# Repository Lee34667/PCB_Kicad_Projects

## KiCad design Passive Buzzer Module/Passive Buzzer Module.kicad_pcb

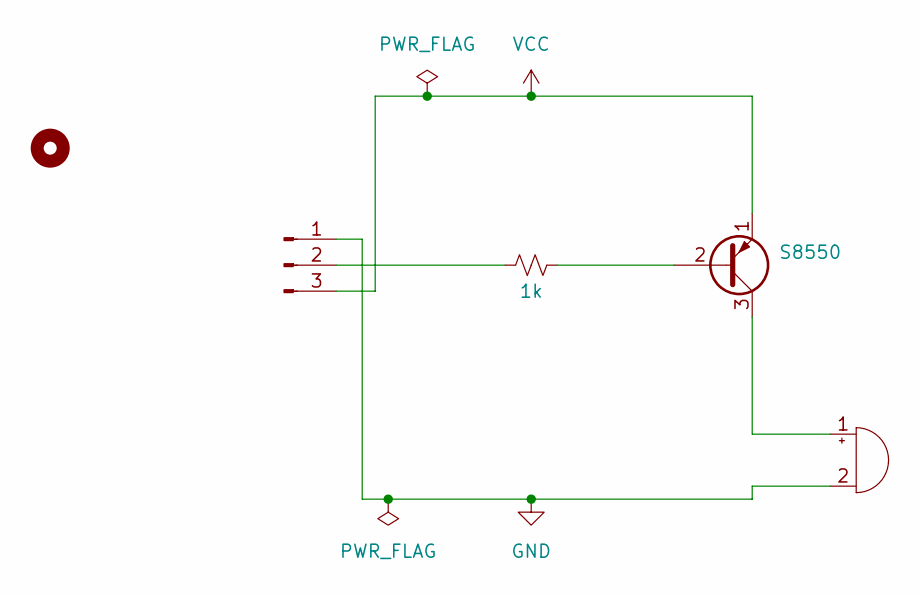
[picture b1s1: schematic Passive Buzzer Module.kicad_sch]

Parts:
BZ1: Buzzer; Buzzer_12x9.5RM7.6
H1: MountingHole; MountingHole_2.1mm
J1: Conn_01x03_Pin; PinHeader_1x03_P2.54mm_Horizontal
Q1: S8550; TO-92_HandSolder
R1: 1k; R_0201_0603Metric

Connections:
GND: BZ1.2 (-), J1.1
unnamed: BZ1.1 (+), Q1.3 (C)
unnamed: J1.2, R1.1
unnamed: Q1.2 (B), R1.2
VCC: J1.3, Q1.1 (E)

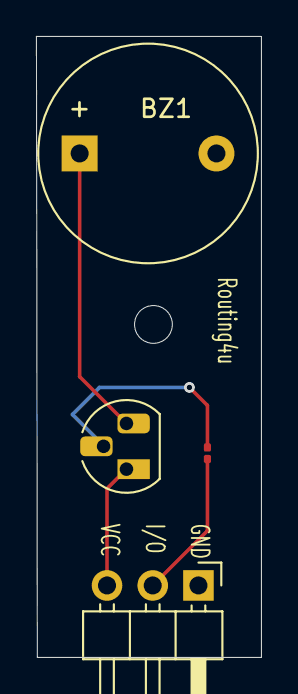
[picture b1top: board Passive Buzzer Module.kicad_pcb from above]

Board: 4 copper layers, 12.5 x 34.5 mm, 5 parts (0 on the bottom side), 5 nets.

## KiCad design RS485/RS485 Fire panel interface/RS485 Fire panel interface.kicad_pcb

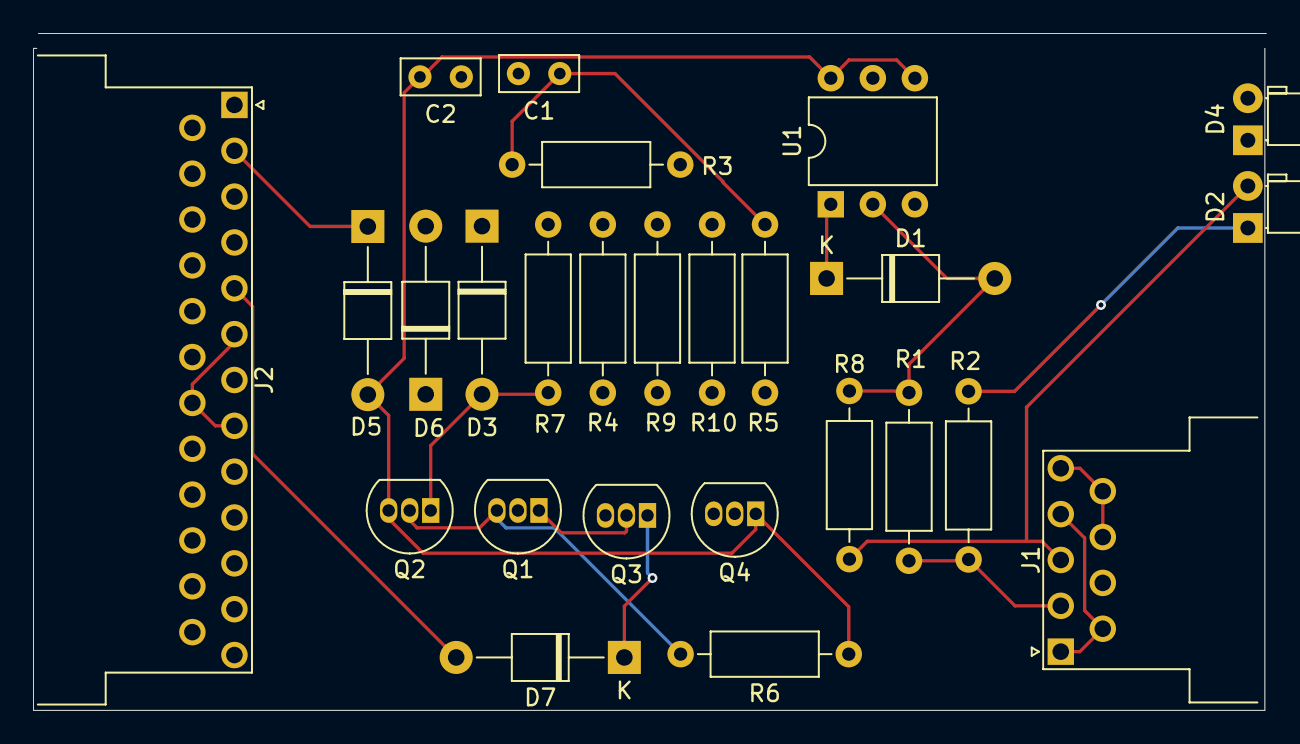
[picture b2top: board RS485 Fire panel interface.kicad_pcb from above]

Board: 2 copper layers, 74.5 x 40.9 mm, 26 parts (0 on the bottom side), 21 nets.

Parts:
C1, C2: 22uF 16V; C_Rect_L4.6mm_W2.0mm_P2.50mm_MKS02_FKP02
D1, D3, D5, D6, D7: D_Filled; D_T-1_P10.16mm_Horizontal
D2: Rx; LED_D3.0mm_Horizontal_O1.27mm_Z2.0mm
D4: Tx; LED_D3.0mm_Horizontal_O1.27mm_Z2.0mm
J1: DE9_Plug; DSUB-9_Male_Horizontal_P2.77x2.54mm_EdgePinOffset9.40mm
J2: DB25_Receptacle; DSUB-25_Male_Horizontal_P2.77x2.54mm_EdgePinOffset9.40mm
Q1, Q2, Q3: BC547; TO-92_Inline
Q4: BC557; TO-92_Inline
R1: 220R; R_Axial_DIN0207_L6.3mm_D2.5mm_P10.16mm_Horizontal
R2: 1k; R_Axial_DIN0207_L6.3mm_D2.5mm_P10.16mm_Horizontal
R3, R4, R5, R6, R7, R8, R9, R10: 2k2; R_Axial_DIN0207_L6.3mm_D2.5mm_P10.16mm_Horizontal
U1: 4N35; DIP-6_W7.62mm

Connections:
GND: C1.2, C2.1, J2.7
unnamed: D1.2 (A), R1.2, R8.1, U1.2
unnamed: D1.1 (K), D2.2 (A), J1.3, R8.2, U1.1
unnamed: D2.1 (K), R2.2
unnamed: D3.2 (A), Q2.1 (C), R7.1
unnamed: D3.1 (K), Q1.2 (B), R4.1, U1.5
unnamed: D4.2 (A), Q3.3 (E)
unnamed: D4.1 (K), R9.2
unnamed: C2.2, D5.2 (A), Q2.3 (E), Q4.1 (C), R6.1, U1.4, U1.6
unnamed: D5.1 (K), J2.2
unnamed: D6.2 (A), J2.6, J2.8, J2.20
unnamed: C1.1, D6.1 (K), D7.1 (K), Q3.1 (C), R3.2, R5.2
unnamed: D7.2 (A), J2.4, J2.5
unnamed: J1.1, J1.4, J1.6
unnamed: J1.2, R1.1, R2.1
unnamed: J1.5, J1.8, J1.9
unnamed: J2.3, R9.1, R10.2
unnamed: Q1.1 (C), Q3.2 (B), Q4.2 (B), R5.1
unnamed: Q1.3 (E), Q2.2 (B), R6.2
unnamed: Q4.3 (E), R10.1
unnamed: R3.1, R4.2, R7.2

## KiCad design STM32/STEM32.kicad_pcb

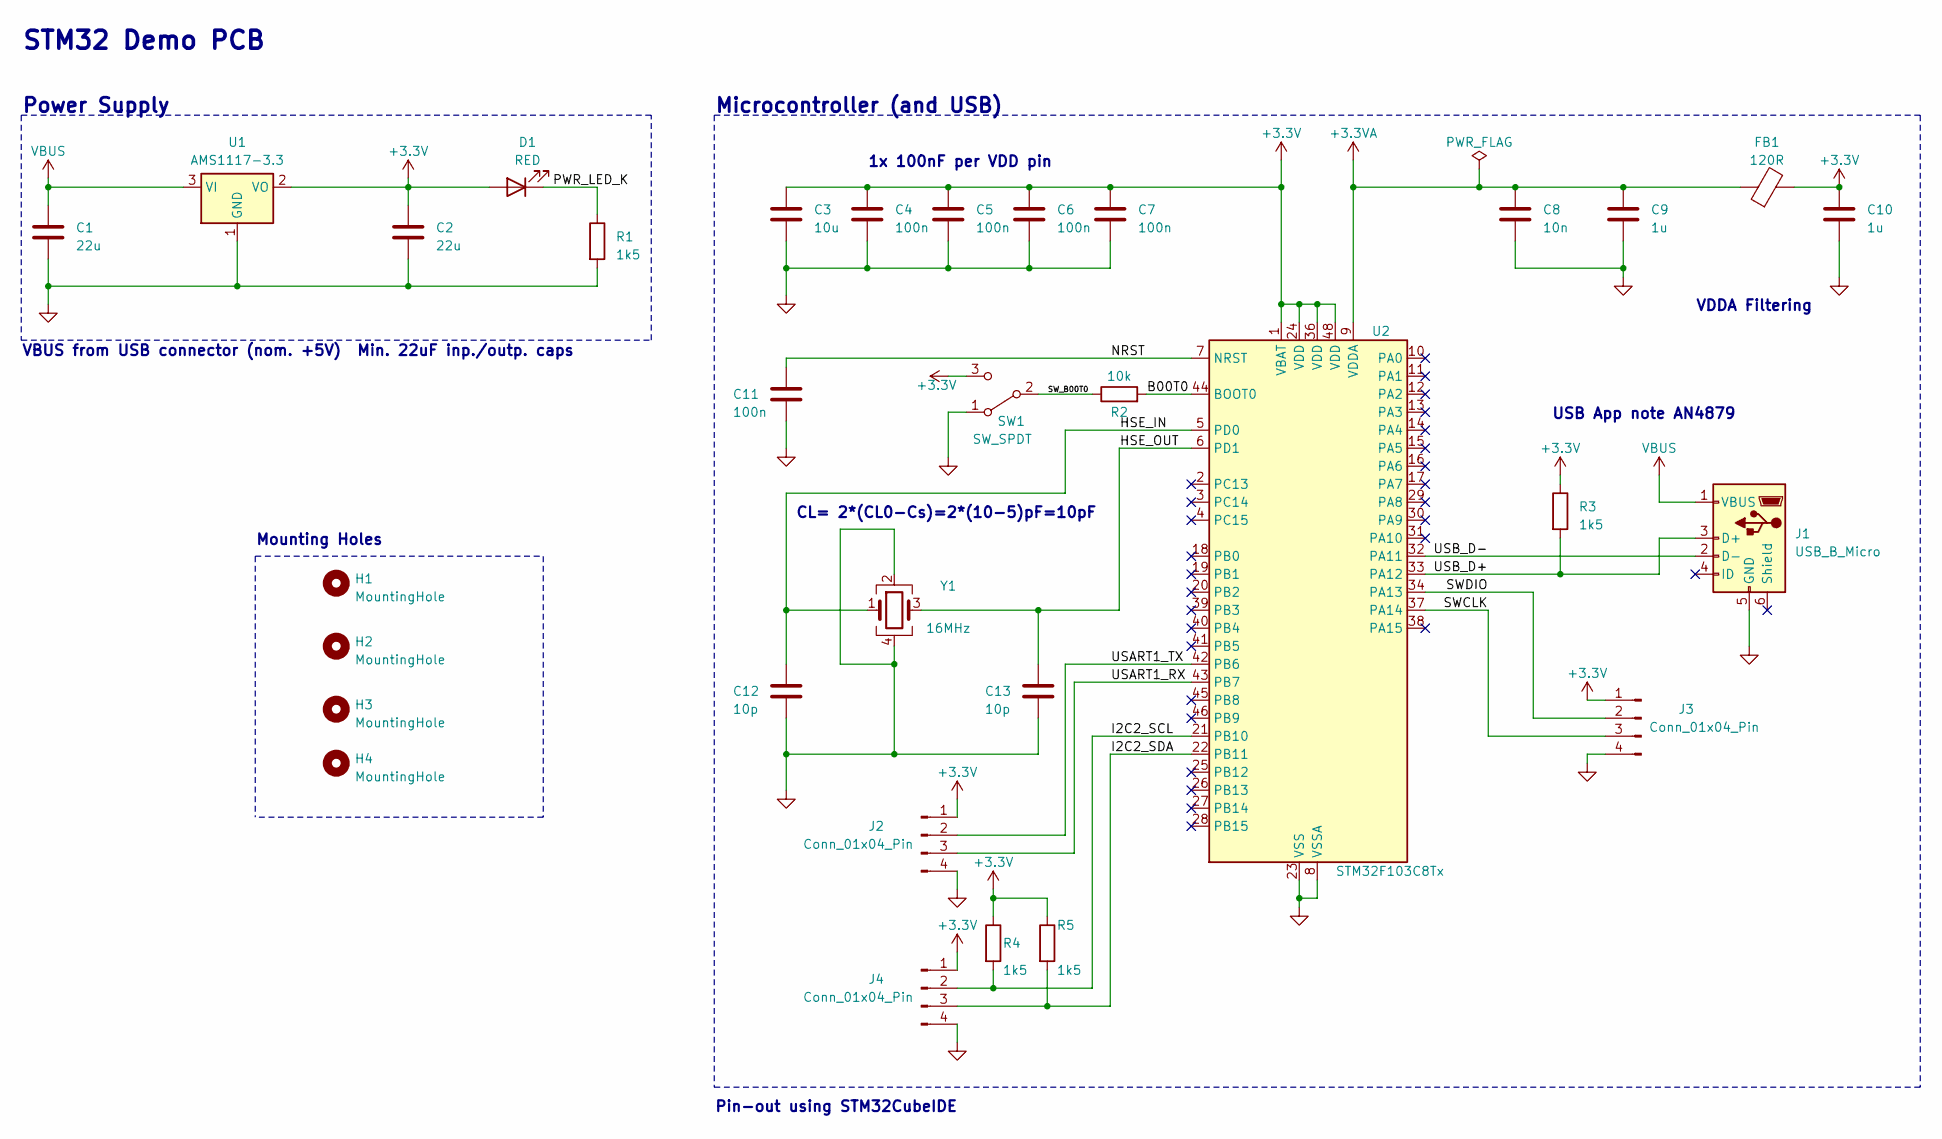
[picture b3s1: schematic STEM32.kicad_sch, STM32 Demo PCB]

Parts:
C1, C2: 22u; C_0805_2012Metric
C3: 10u; C_0603_1608Metric
C4, C5, C6, C7, C11: 100n; C_0402_1005Metric
C8: 10n; C_0402_1005Metric
C9, C10: 1u; C_0402_1005Metric
C12, C13: 10p; C_0402_1005Metric
D1: RED; LED_0603_1608Metric
FB1: 120R; L_0603_1608Metric
H1, H2, H3, H4: MountingHole; MountingHole_2.2mm_M2
J1: USB_B_Micro; USB_Micro-B_Wuerth_629105150521
J2, J3, J4: Conn_01x04_Pin; PinHeader_1x04_P2.54mm_Vertical
R1, R3, R4, R5: 1k5; R_0402_1005Metric
R2: 10k; R_0402_1005Metric
SW1: SW_SPDT; SW_SPDT_PCM12
U1: AMS1117-3.3; SOT-223-3_TabPin2
U2: STM32F103C8Tx; LQFP-48_7x7mm_P0.5mm
Y1: 16MHz; Crystal_SMD_3225-4Pin_3.2x2.5mm

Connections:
+3.3V: C2.1, C3.1, C4.1, C5.1, C6.1, C7.1, C10.1, D1.2 (A), FB1.2, J2.1, J3.1, J4.1, R3.1, R4.1, R5.1, SW1.3 (C), U1.2 (VO), U2.1 (VBAT), U2.24 (VDD), U2.36 (VDD), U2.48 (VDD)
+3.3VA: C8.1, C9.1, FB1.1, U2.9 (VDDA)
/B00T0: R2.2, U2.44 (BOOT0)
/HSE_IN: C12.1, U2.5 (PD0), Y1.1
/HSE_OUT: C13.1, U2.6 (PD1), Y1.3
/I2C2_SCL: J4.2, R4.2, U2.21 (PB10)
/I2C2_SDA: J4.3, R5.2, U2.22 (PB11)
/NRST: C11.1, U2.7 (NRST)
/PWR_LED_K: D1.1 (K), R1.1
/SWCLK: J3.3, U2.37 (PA14)
/SWDIO: J3.2, U2.34 (PA13)
/SW_B00T0: R2.1, SW1.2 (B)
/USART1_RX: J2.3, U2.43 (PB7)
/USART1_TX: J2.2, U2.42 (PB6)
/USB_D+: J1.3 (D+), R3.2, U2.33 (PA12)
/USB_D-: J1.2 (D-), U2.32 (PA11)
GND: C1.2, C2.2, C3.2, C4.2, C5.2, C6.2, C7.2, C8.2, C9.2, C10.2, C11.2, C12.2, C13.2, J1.5 (GND), J2.4, J3.4, J4.4, R1.2, SW1.1 (A), U1.1 (GND), U2.8 (VSSA), U2.23 (VSS), U2.35 (VSS), U2.47 (VSS), Y1.2, Y1.4
VBUS: C1.1, J1.1 (VBUS), U1.3 (VI)

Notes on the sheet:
VBUS from USB connector (nom. +5V) Min. 22uF inp./outp. caps
USB App note AN4879
1x 100nF per VDD pin
Microcontroller (and USB)
VDDA Filtering
Mounting Holes
CL= 2*(CL0-Cs)=2*(10-5)pF=10pF
Pin-out using STM32CubeIDE
Power Supply
STM32 Demo PCB

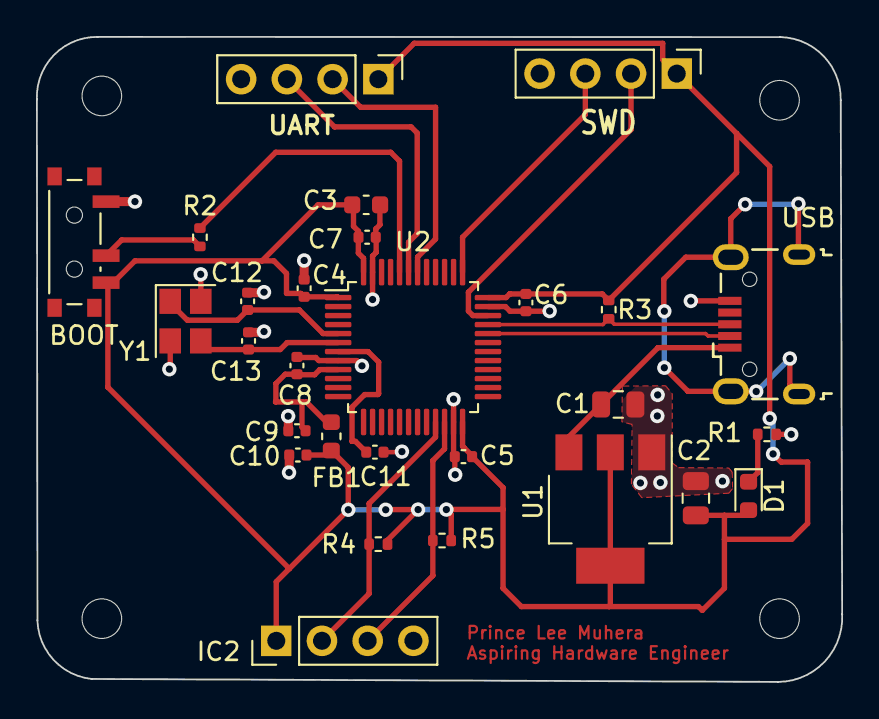
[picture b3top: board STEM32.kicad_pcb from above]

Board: 2 copper layers, 44.7 x 35.8 mm, 32 parts (0 on the bottom side), 18 nets.

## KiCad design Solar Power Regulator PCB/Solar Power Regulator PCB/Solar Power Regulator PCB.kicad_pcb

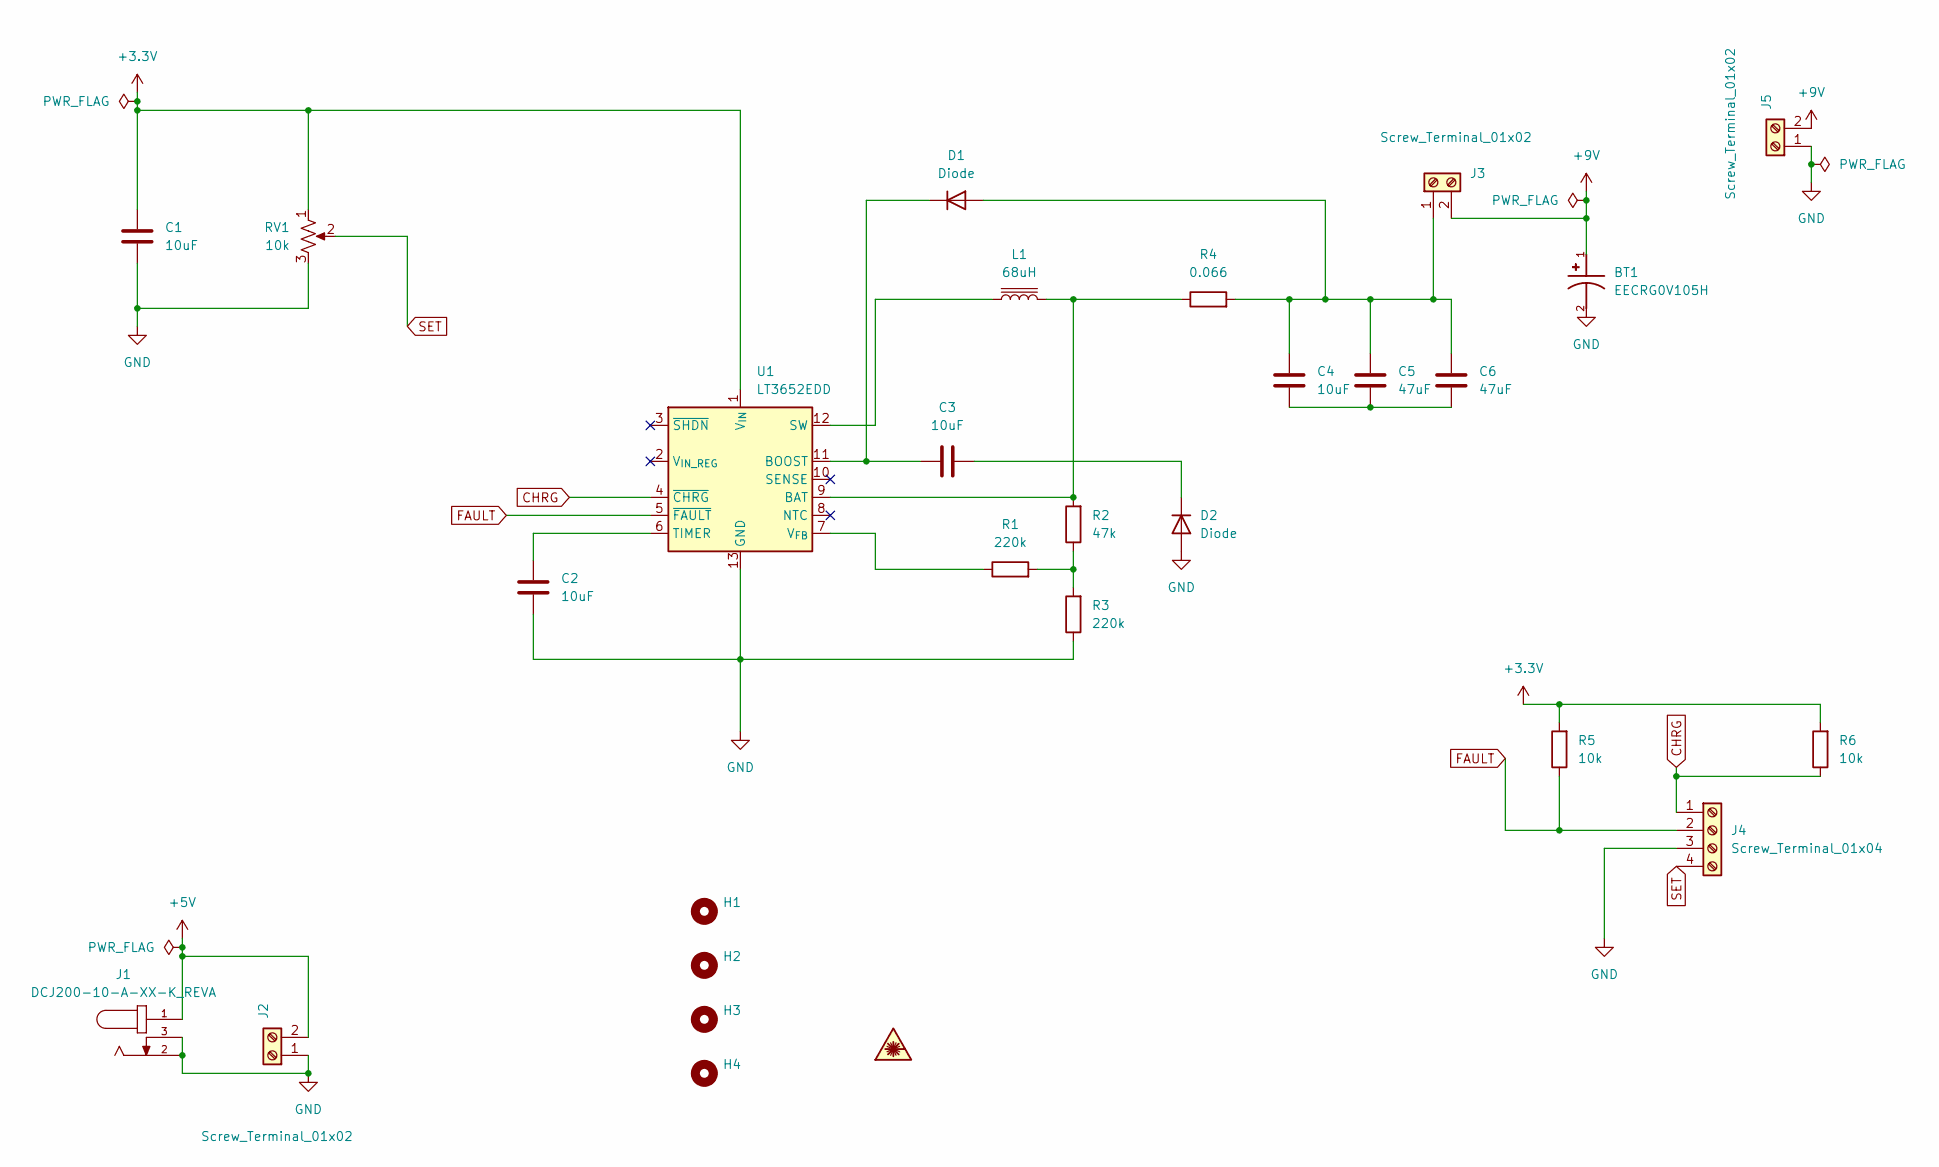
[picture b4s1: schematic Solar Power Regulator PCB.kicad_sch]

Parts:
BT1: EECRG0V105H; CAPRD2000W100L650D1900; PARTREV N/A
C1: 10uF; C_Rect_L10.0mm_W2.5mm_P7.50mm_MKS4
C2, C3: 10uF; C_Disc_D5.1mm_W3.2mm_P5.00mm
C4: 10uF; C_Radial_D5.0mm_H7.0mm_P2.00mm
C5: 47uF; C_Radial_D5.0mm_H7.0mm_P2.00mm
C6: 47uF; C_Rect_L10.0mm_W2.5mm_P7.50mm_MKS4
D1, D2: Diode; D_A-405_P7.62mm_Horizontal
H1, H2, H3, H4: MountingHole; MountingHole_2.5mm
J1: DCJ200-10-A-XX-K_REVA; GCT_DCJ200-10-A-XX-K_REVA; PARTREV A
J2, J3, J5: Screw_Terminal_01x02; TerminalBlock_Phoenix_MKDS-1,5-2_1x02_P5.00mm_Horizontal
J4: Screw_Terminal_01x04; TerminalBlock_Phoenix_MKDS-1,5-4_1x04_P5.00mm_Horizontal
L1: 68uH; L_1812_4532Metric_Pad1.30x3.40mm_HandSolder
R1, R3: 220k; R_2512_6332Metric_Pad1.40x3.35mm_HandSolder
R2: 47k; R_2512_6332Metric_Pad1.40x3.35mm_HandSolder
R4: 0.066; R_2512_6332Metric_Pad1.40x3.35mm_HandSolder
R5, R6: 10k; R_2512_6332Metric_Pad1.40x3.35mm_HandSolder
RV1: 10k; Potentiometer_Bourns_TC33X_Vertical
U1: LT3652EDD; DFN-12-1EP_3x3mm_P0.45mm_EP1.65x2.38mm

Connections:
+3.3V: C1.1, R5.2, R6.2, RV1.1, U1.1 (V_{IN})
+5V: J1.1, J2.2
+9V: BT1.1, J3.2, J5.2
CHRG: J4.1, R6.1, U1.4 (~CHRG)
FAULT: J4.2, R5.1, U1.5 (~FAULT)
GND: BT1.2, C1.2, C2.2, D2.2 (A), J1.2, J1.3, J2.1, J4.3, J5.1, R3.1, RV1.3, U1.13 (GND)
unnamed: C4.2, C5.2, C6.2
unnamed: C4.1, C5.1, C6.1, D1.2 (A), J3.1, R4.2
unnamed: C3.1, D1.1 (K), U1.11 (BOOST)
unnamed: C3.2, D2.1 (K)
unnamed: R1.2, R2.1, R3.2
unnamed: L1.2, R2.2, R4.1, U1.9 (BAT)
unnamed: L1.1, U1.12 (SW)
unnamed: C2.1, U1.6 (TIMER)
unnamed: R1.1, U1.7 (V_{FB})
SET: J4.4, RV1.2

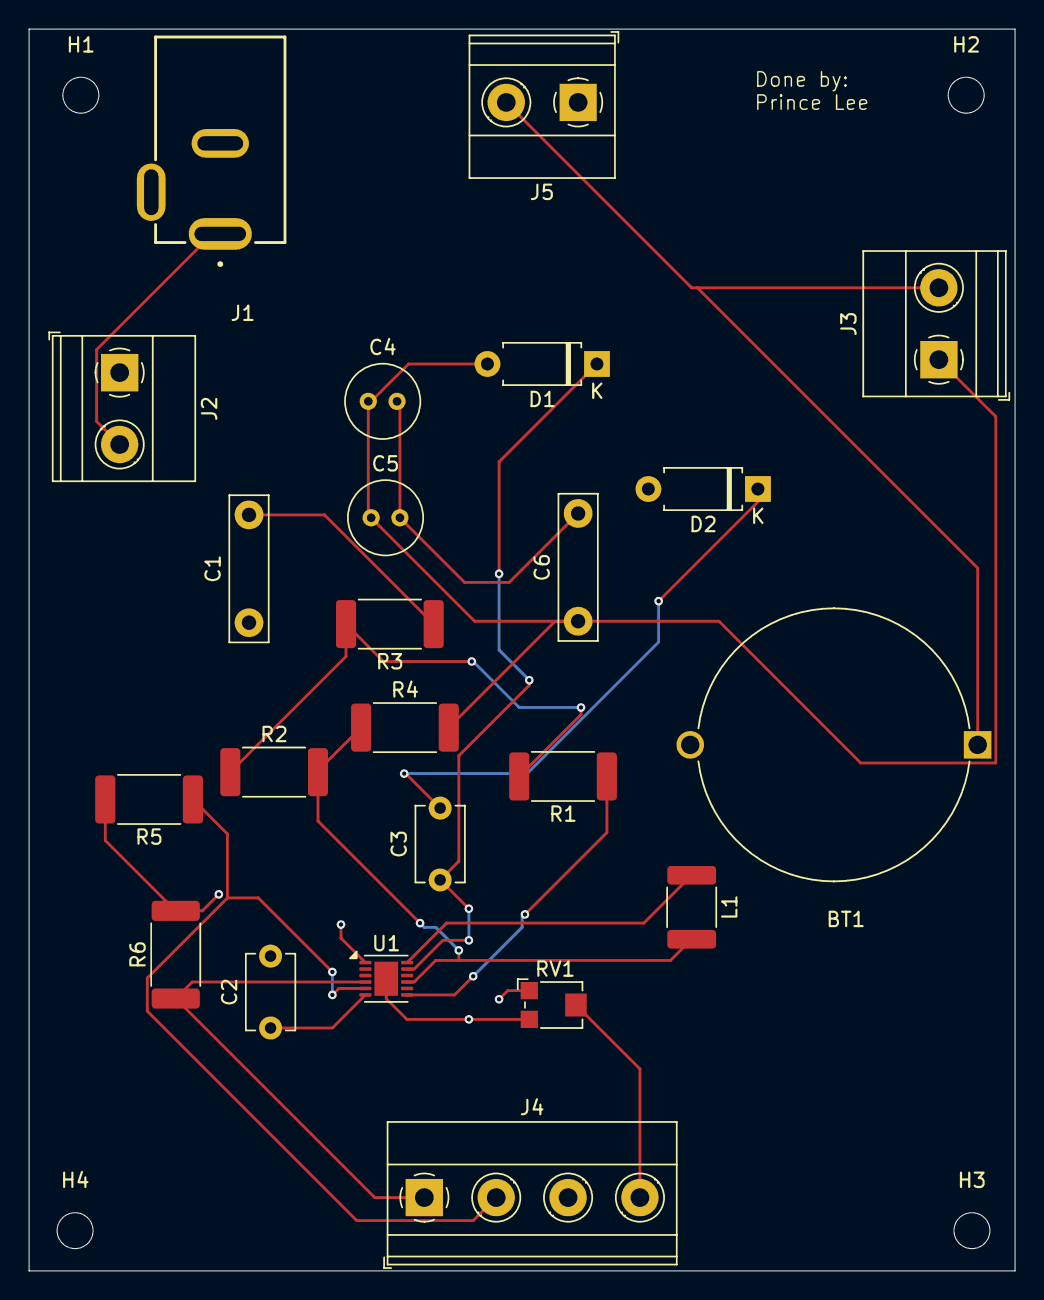
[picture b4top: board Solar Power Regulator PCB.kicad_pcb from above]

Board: 4 copper layers, 68.6 x 86.4 mm, 27 parts (0 on the bottom side), 16 nets.

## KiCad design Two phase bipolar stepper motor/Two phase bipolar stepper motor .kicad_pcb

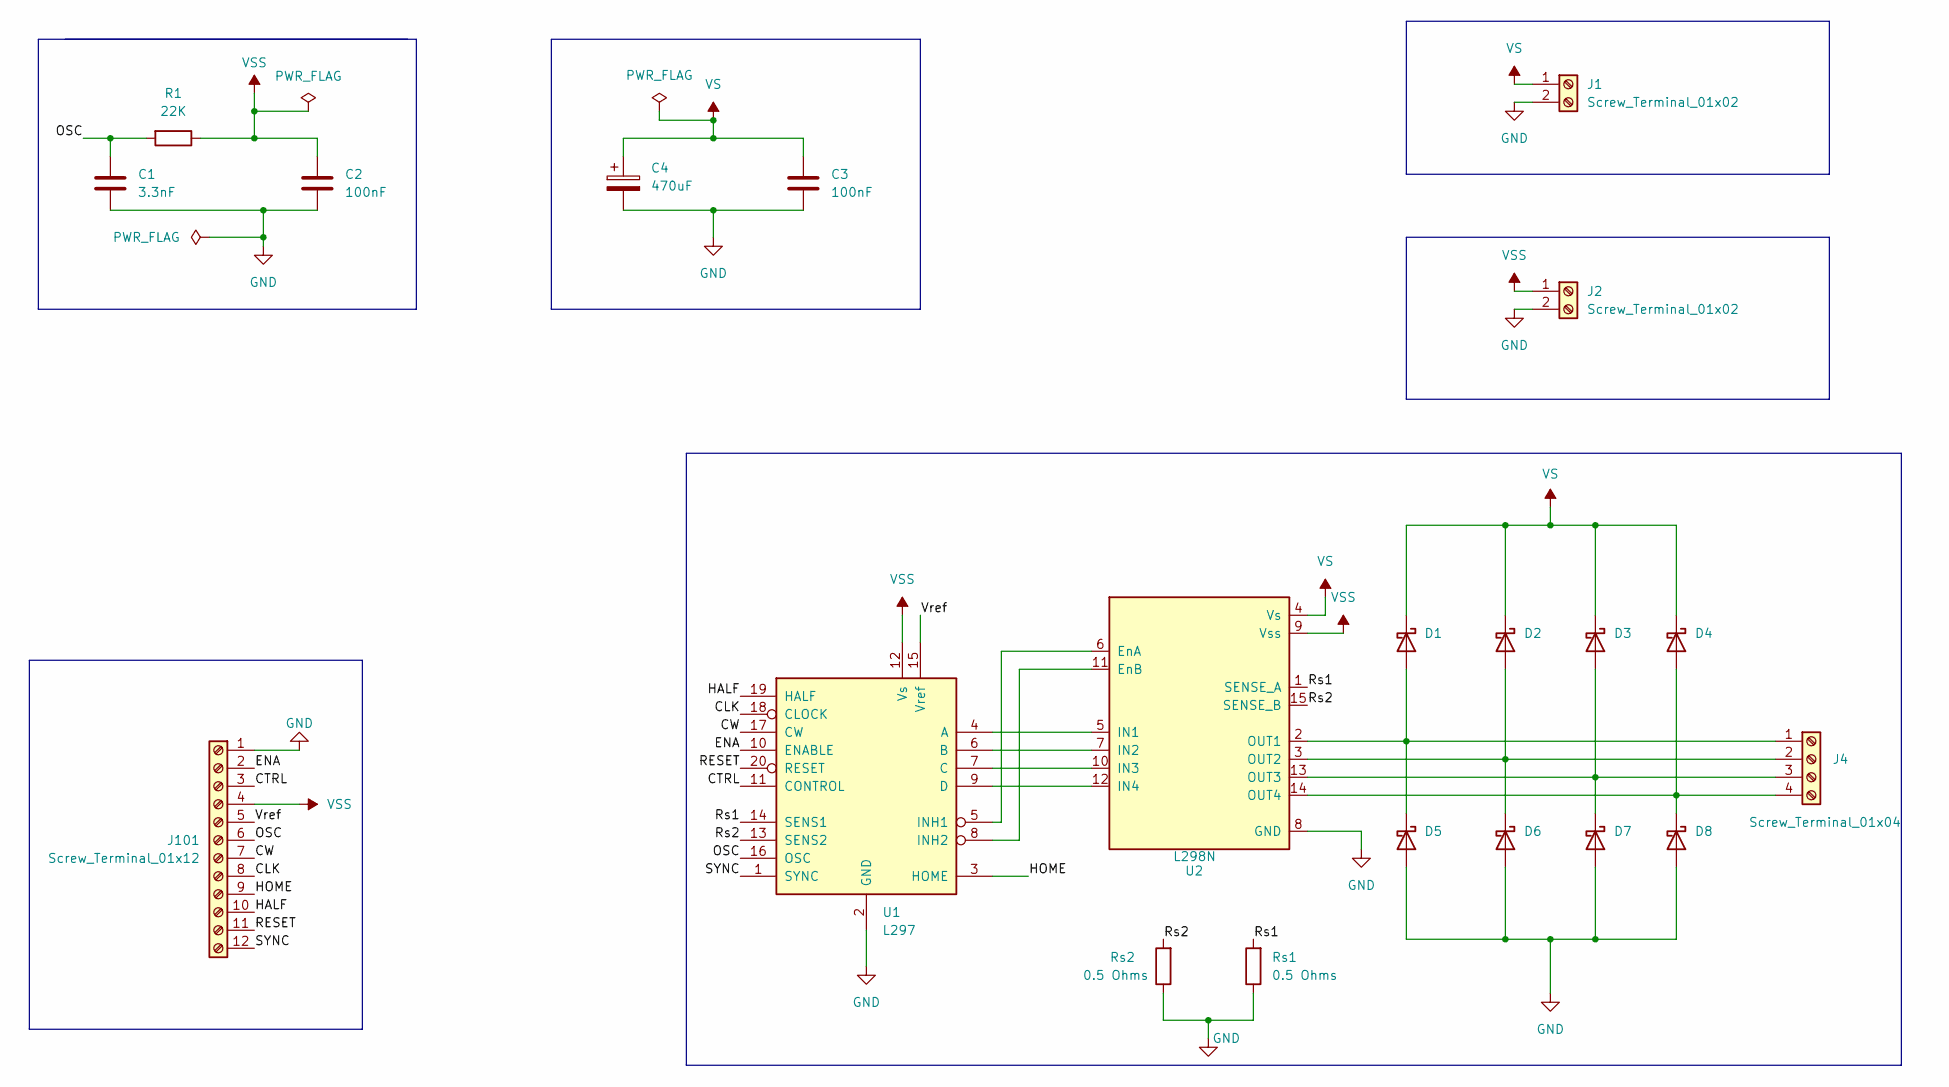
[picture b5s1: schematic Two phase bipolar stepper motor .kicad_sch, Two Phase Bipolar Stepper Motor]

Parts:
C1: 3.3nF; C_Rect_L10.0mm_W3.0mm_P7.50mm_MKS4
C2, C3: 100nF; C_Rect_L10.0mm_W2.5mm_P7.50mm_MKS4
C4: 470uF; CP_Radial_D13.0mm_P5.00mm
D1, D2, D3, D4, D5, D6, D7, D8: D_DO-27_P15.24mm_Horizontal
J1, J2: Screw_Terminal_01x02; TerminalBlock_Phoenix_MKDS-1,5-2-5.08_1x02_P5.08mm_Horizont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
J4: Screw_Terminal_01x04; TerminalBlock_Phoenix_MKDS-1,5-4_1x04_P5.00mm_Horizontal
J101: Screw_Terminal_01x12; TerminalBlock_Phoenix_MKDS-1,5-12-5.08_1x12_P5.08mm_Horizon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
R1: 22K; R_Axial_DIN0414_L11.9mm_D4.5mm_P15.24mm_Horizontal
Rs1, Rs2: 0.5 Ohms; R_Axial_DIN0414_L11.9mm_D4.5mm_P15.24mm_Horizontal
U1: L297; DIP-20_W7.62mm_LongPads
U2: L298N; TO127P2020X500X2100-15

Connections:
/CLK: J101.8, U1.18 (CLOCK)
/CTRL: J101.3, U1.11 (CONTROL)
/CW: J101.7, U1.17 (CW)
/ENA: J101.2, U1.10 (ENABLE)
/HALF: J101.10, U1.19 (HALF)
/HOME: J101.9, U1.3 (HOME)
/OSC: C1.1, J101.6, R1.2, U1.16 (OSC)
/RESET: J101.11, U1.20 (RESET)
/Rs1: Rs1.2, U1.14 (SENS1), U2.1 (SENSE_A)
/Rs2: Rs2.2, U1.13 (SENS2), U2.15 (SENSE_B)
/SYNC: J101.12, U1.1 (SYNC)
/Vref: J101.5, U1.15 (Vref)
GND: C1.2, C2.2, C3.1, C4.2, D5.2 (A), D6.2 (A), D7.2 (A), D8.2 (A), J1.2, J2.2, J101.1, Rs1.1, Rs2.1, U1.2 (GND), U2.8 (GND)
unnamed: D1.2 (A), D5.1 (K), J4.1, U2.2 (OUT1)
unnamed: D2.2 (A), D6.1 (K), J4.2, U2.3 (OUT2)
unnamed: D3.2 (A), D7.1 (K), J4.3, U2.13 (OUT3)
unnamed: D4.2 (A), D8.1 (K), J4.4, U2.14 (OUT4)
unnamed: U1.4 (A), U2.5 (IN1)
unnamed: U1.6 (B), U2.7 (IN2)
unnamed: U1.7 (C), U2.10 (IN3)
unnamed: U1.9 (D), U2.12 (IN4)
unnamed: U1.5 (INH1), U2.6 (EnA)
unnamed: U1.8 (INH2), U2.11 (EnB)
VS: C3.2, C4.1, D1.1 (K), D2.1 (K), D3.1 (K), D4.1 (K), J1.1, U2.4 (Vs)
VSS: C2.1, J2.1, J101.4, R1.1, U1.12 (Vs), U2.9 (Vss)

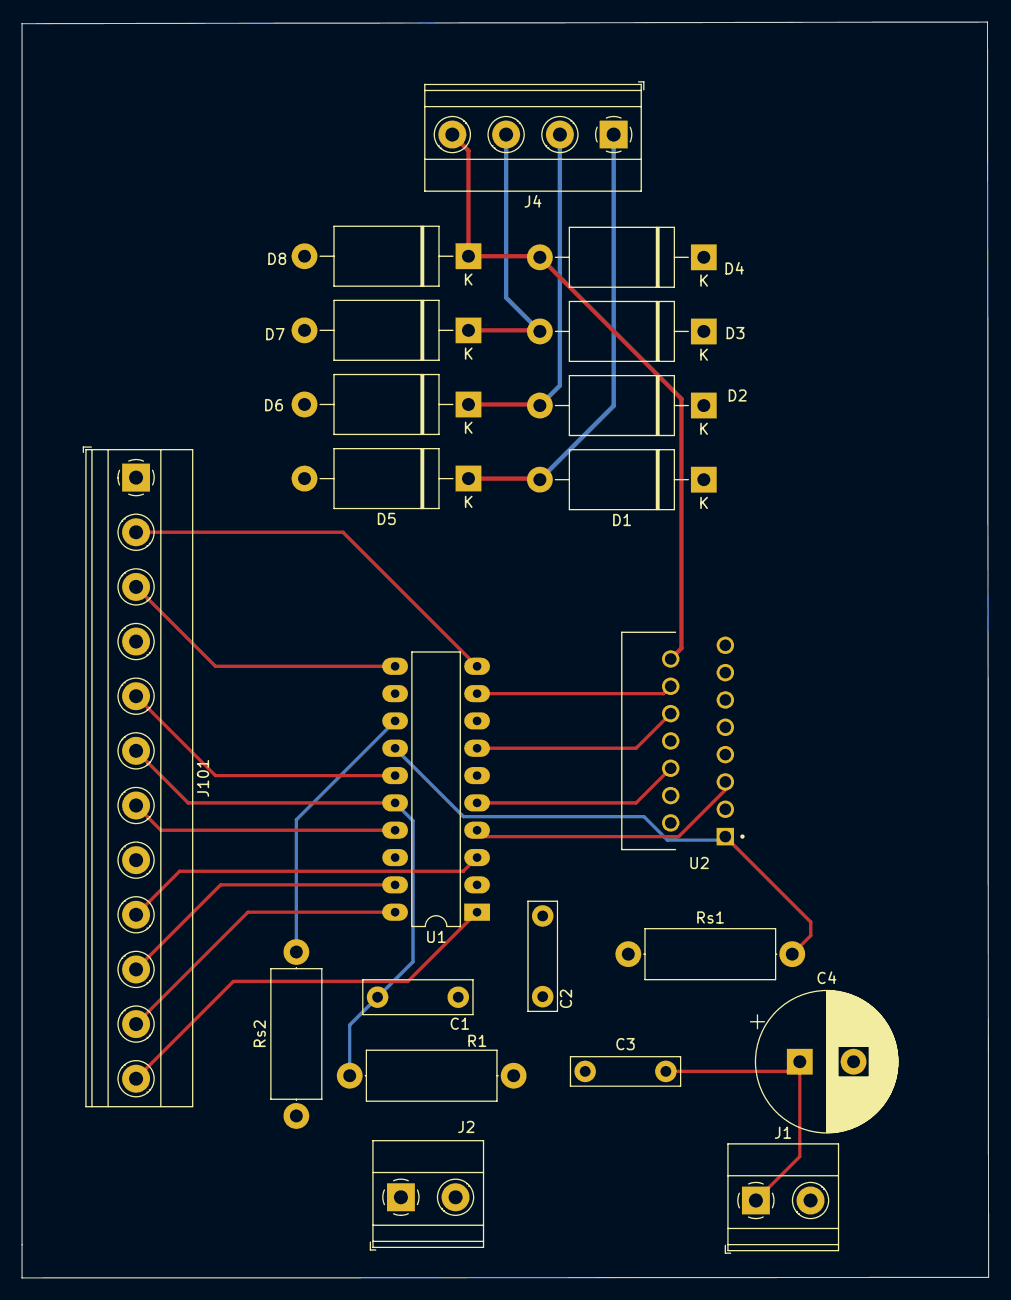
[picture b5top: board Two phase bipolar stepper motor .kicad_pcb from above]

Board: 8 copper layers, 89.8 x 116.8 mm, 21 parts (0 on the bottom side), 25 nets.

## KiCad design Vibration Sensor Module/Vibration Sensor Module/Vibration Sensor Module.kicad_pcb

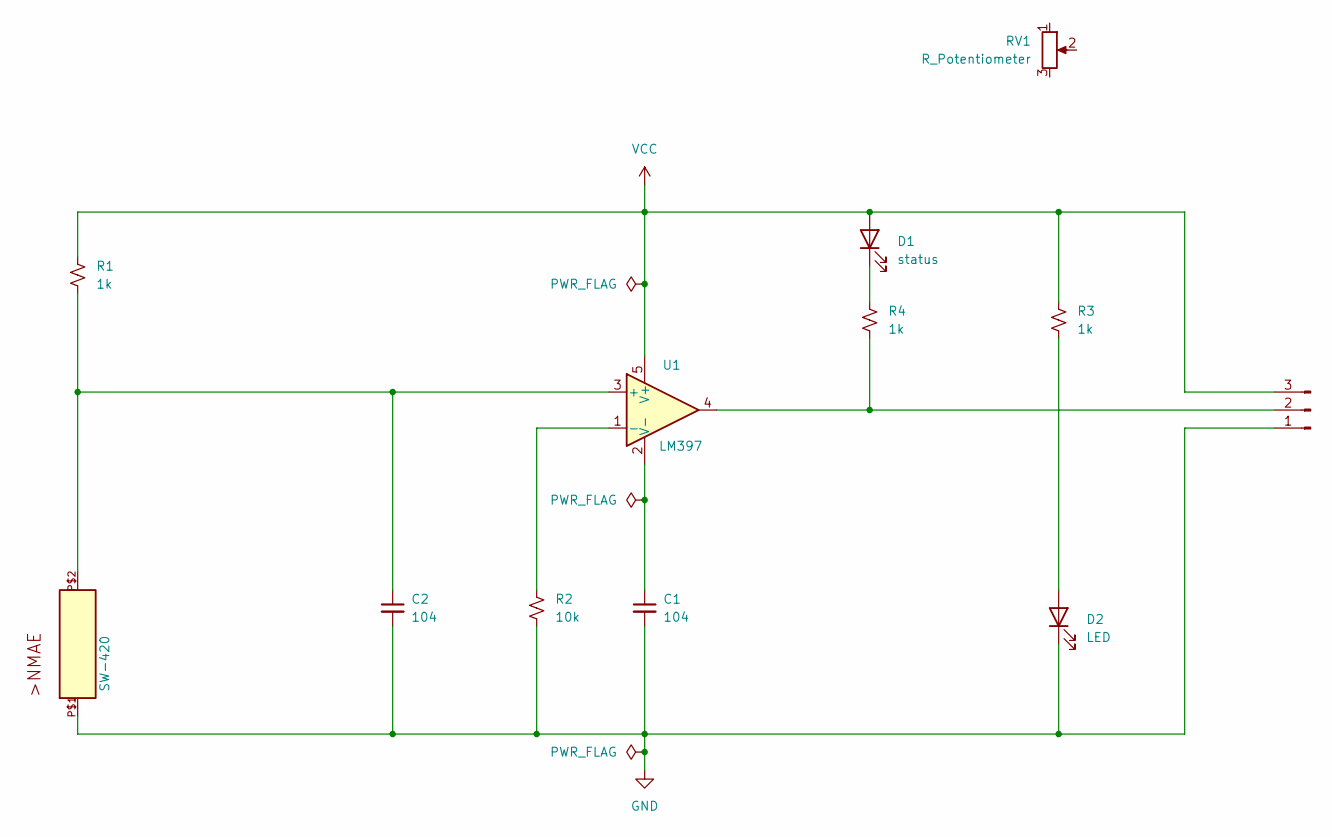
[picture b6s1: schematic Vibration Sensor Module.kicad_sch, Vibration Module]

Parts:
C1, C2: 104; C_0201_0603Metric
D1: status; LED_0201_0603Metric
D2: LED; LED_0201_0603Metric
J1: Conn_01x03_Pin; PinHeader_1x03_P2.54mm_Horizontal
R1, R3, R4: 1k; R_0201_0603Metric
R2: 10k; R_0201_0603Metric
RV1: R_Potentiometer
U1: LM397; SOT-23-5
X1: SW-420

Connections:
GND: C1.2, C2.2, D2.1 (K), J1.1, R2.2, X1.P$1
unnamed: D1.1 (K), R4.1
unnamed: D2.2 (A), R3.2
unnamed: J1.2, R4.2, U1.4
unnamed: C2.1, R1.2, U1.3 (+), X1.P$2
unnamed: R2.1, U1.1 (-)
unnamed: C1.1, U1.2 (V-)
VCC: D1.2 (A), J1.3, R1.1, R3.1, U1.5 (V+)

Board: 2 copper layers, 11 parts (0 on the bottom side), 8 nets, no tracks yet.
